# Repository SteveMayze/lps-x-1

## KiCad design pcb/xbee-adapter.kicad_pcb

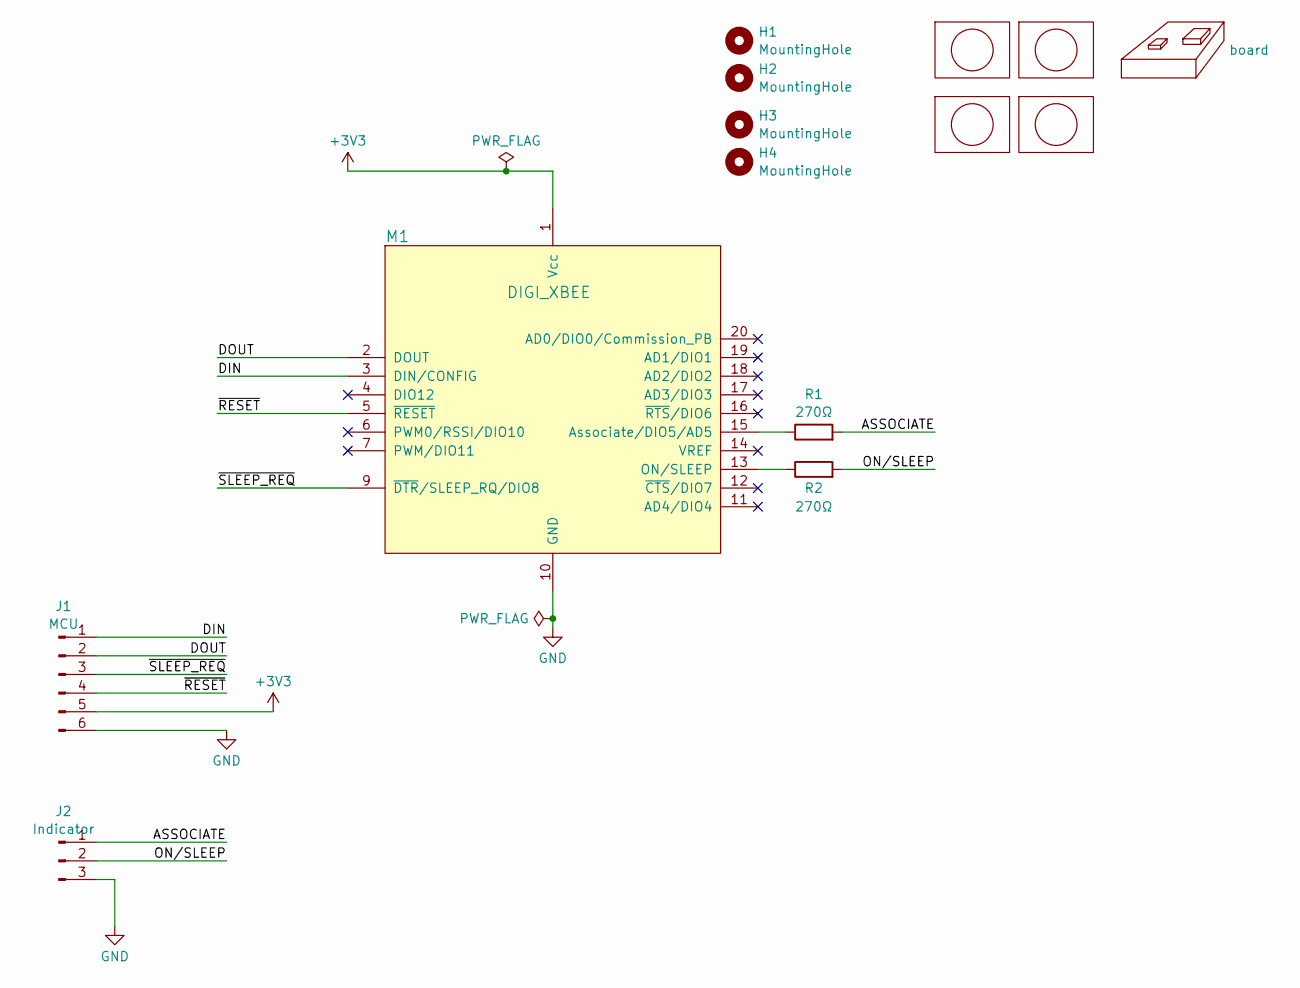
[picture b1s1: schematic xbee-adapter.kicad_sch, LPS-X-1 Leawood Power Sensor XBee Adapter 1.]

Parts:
Brd1: board; Board Ref
H1, H2, H3, H4: MountingHole; MountingHole_2.7mm_M2.5_DIN965
J1: MCU; PinHeader_2x03_P2.54mm_Vertical
J2: Indicator; PinHeader_1x03_P2.54mm_Vertical
Lg1, Lg3: logo; KiCad-Logo2_5mm_SilkScreen
Lg2, Lg4: logo; MyBasic_rounded_50_1
M1: DIGI_XBEE; XBEE_S2C
R1, R2: 270Ω; R_0805_2012Metric

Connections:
+3V3: J1.5, M1.1 (Vcc)
/ASSOCIATE: J2.1, R1.2
/DIN: J1.1, M1.3 (DIN/CONFIG)
/DOUT: J1.2, M1.2 (DOUT)
/ON/SLEEP: J2.2, R2.2
/~RESET: J1.4, M1.5 (~RESET)
/~SLEEP_REQ: J1.3, M1.9 (~DTR/SLEEP_RQ/DIO8)
GND: J1.6, J2.3, M1.10 (GND)
unnamed: M1.15 (Associate/DIO5/AD5), R1.1
unnamed: M1.13 (ON/SLEEP), R2.1

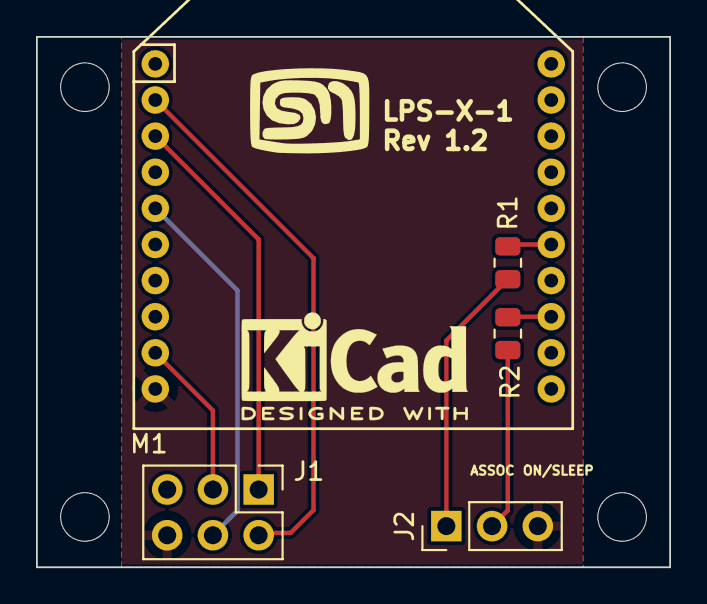
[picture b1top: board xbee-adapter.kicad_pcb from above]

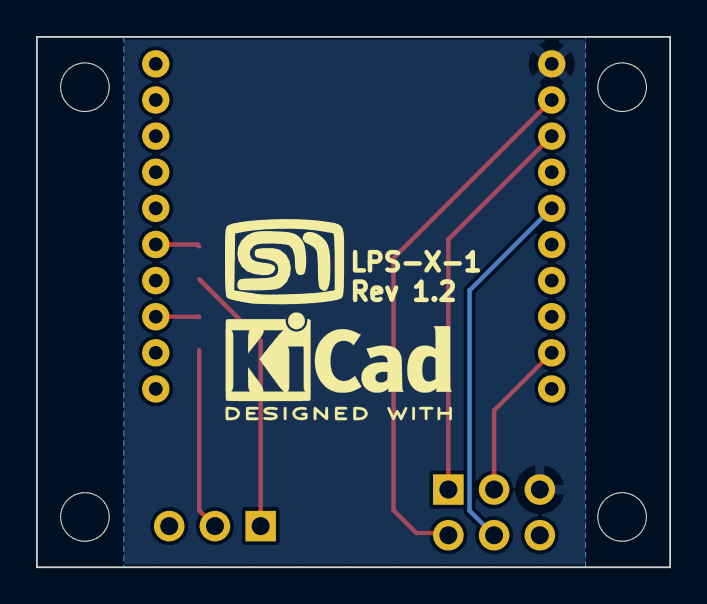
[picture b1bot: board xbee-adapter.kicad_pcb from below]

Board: 2 copper layers, 35.2 x 29.5 mm, 14 parts (2 on the bottom side), 10 nets.

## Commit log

2024-01-28 Revision 1 checkin
2024-01-30 Adds resistors for the indicator LEDs
2024-05-15 Adds a ground pin for the inticator connector
